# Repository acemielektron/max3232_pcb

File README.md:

# max3232_pcb
diy single sided pcb for max3232 RS232 to TTL serial

After cheap max3232 pcb was broken i have placed components with the addtion of 3.3k resistors on rs232 inputs on a diy pcb.

Why 3.3k resistors? because these cheap max3232 clones cause crosstalk while connected to a PC RS232 port. 
This was en effective solution. And with the new pcb i added rts and cts.

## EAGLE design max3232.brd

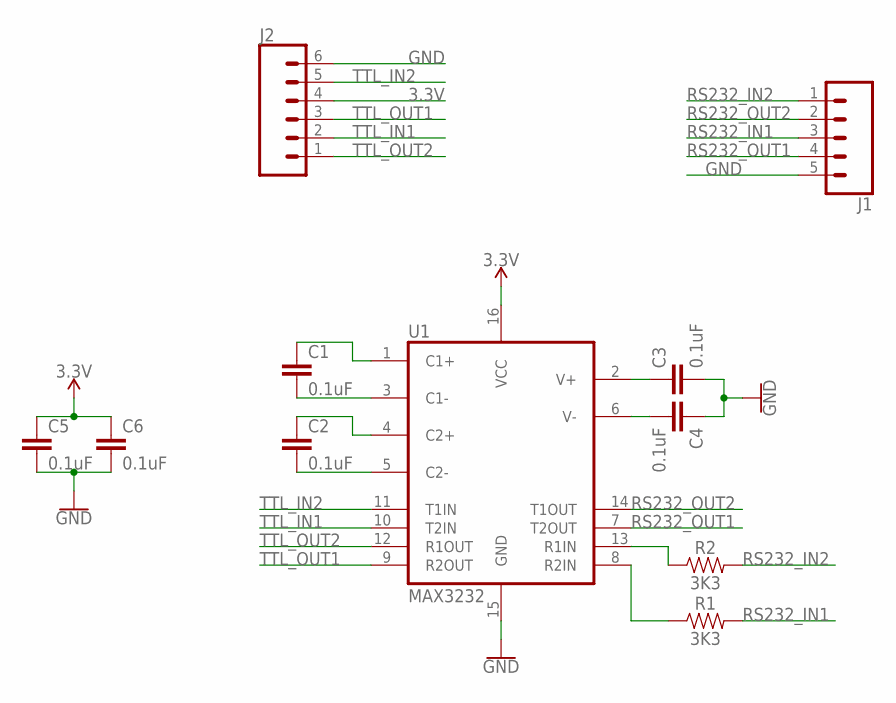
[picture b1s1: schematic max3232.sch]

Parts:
C1, C2, C3, C4, C5, C6: 0.1uF; 0805
J1: CONN_05; 1X05
J2: CONN_06SILK_FEMALE_PTH; 1X06
R1, R2: 3K3; 1206
U1: MAX3232; SO16

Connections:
3.3V: C5.1, C6.1, J2.4, U1.16 (VCC)
GND: C3.2, C4.1, C5.2, C6.2, J1.5, J2.6, U1.15 (GND)
unnamed: C3.1, U1.2 (V+)
unnamed: C1.2, U1.3 (C1-)
unnamed: C1.1, U1.1 (C1+)
unnamed: C2.2, U1.5 (C2-)
unnamed: C2.1, U1.4 (C2+)
unnamed: C4.2, U1.6 (V-)
unnamed: R2.1, U1.13 (R1IN)
unnamed: R1.1, U1.8 (R2IN)
RS232_IN1: J1.3, R1.2
RS232_IN2: J1.1, R2.2
RS232_OUT1: J1.4, U1.7 (T2OUT)
RS232_OUT2: J1.2, U1.14 (T1OUT)
TTL_IN1: J2.2, U1.10 (T2IN)
TTL_IN2: J2.5, U1.11 (T1IN)
TTL_OUT1: J2.3, U1.9 (R2OUT)
TTL_OUT2: J2.1, U1.12 (R1OUT)

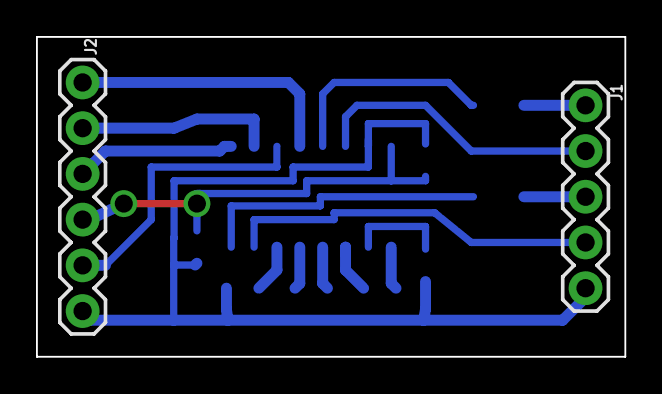
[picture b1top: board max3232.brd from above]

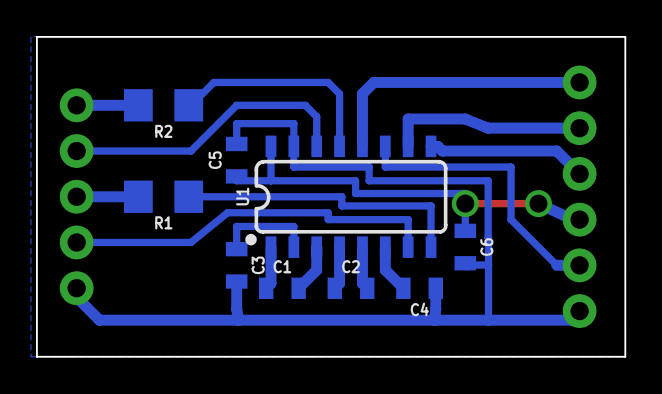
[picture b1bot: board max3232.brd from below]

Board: 2 copper layers, 32.7 x 17.8 mm, 11 parts (9 on the bottom side), 18 nets.

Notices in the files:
parts and their libraries:
SparkFun-Capacitors: Licensing: Creative Commons ShareAlike 4.0 International - https://creativecommons.org/licenses/by-sa/4.0
